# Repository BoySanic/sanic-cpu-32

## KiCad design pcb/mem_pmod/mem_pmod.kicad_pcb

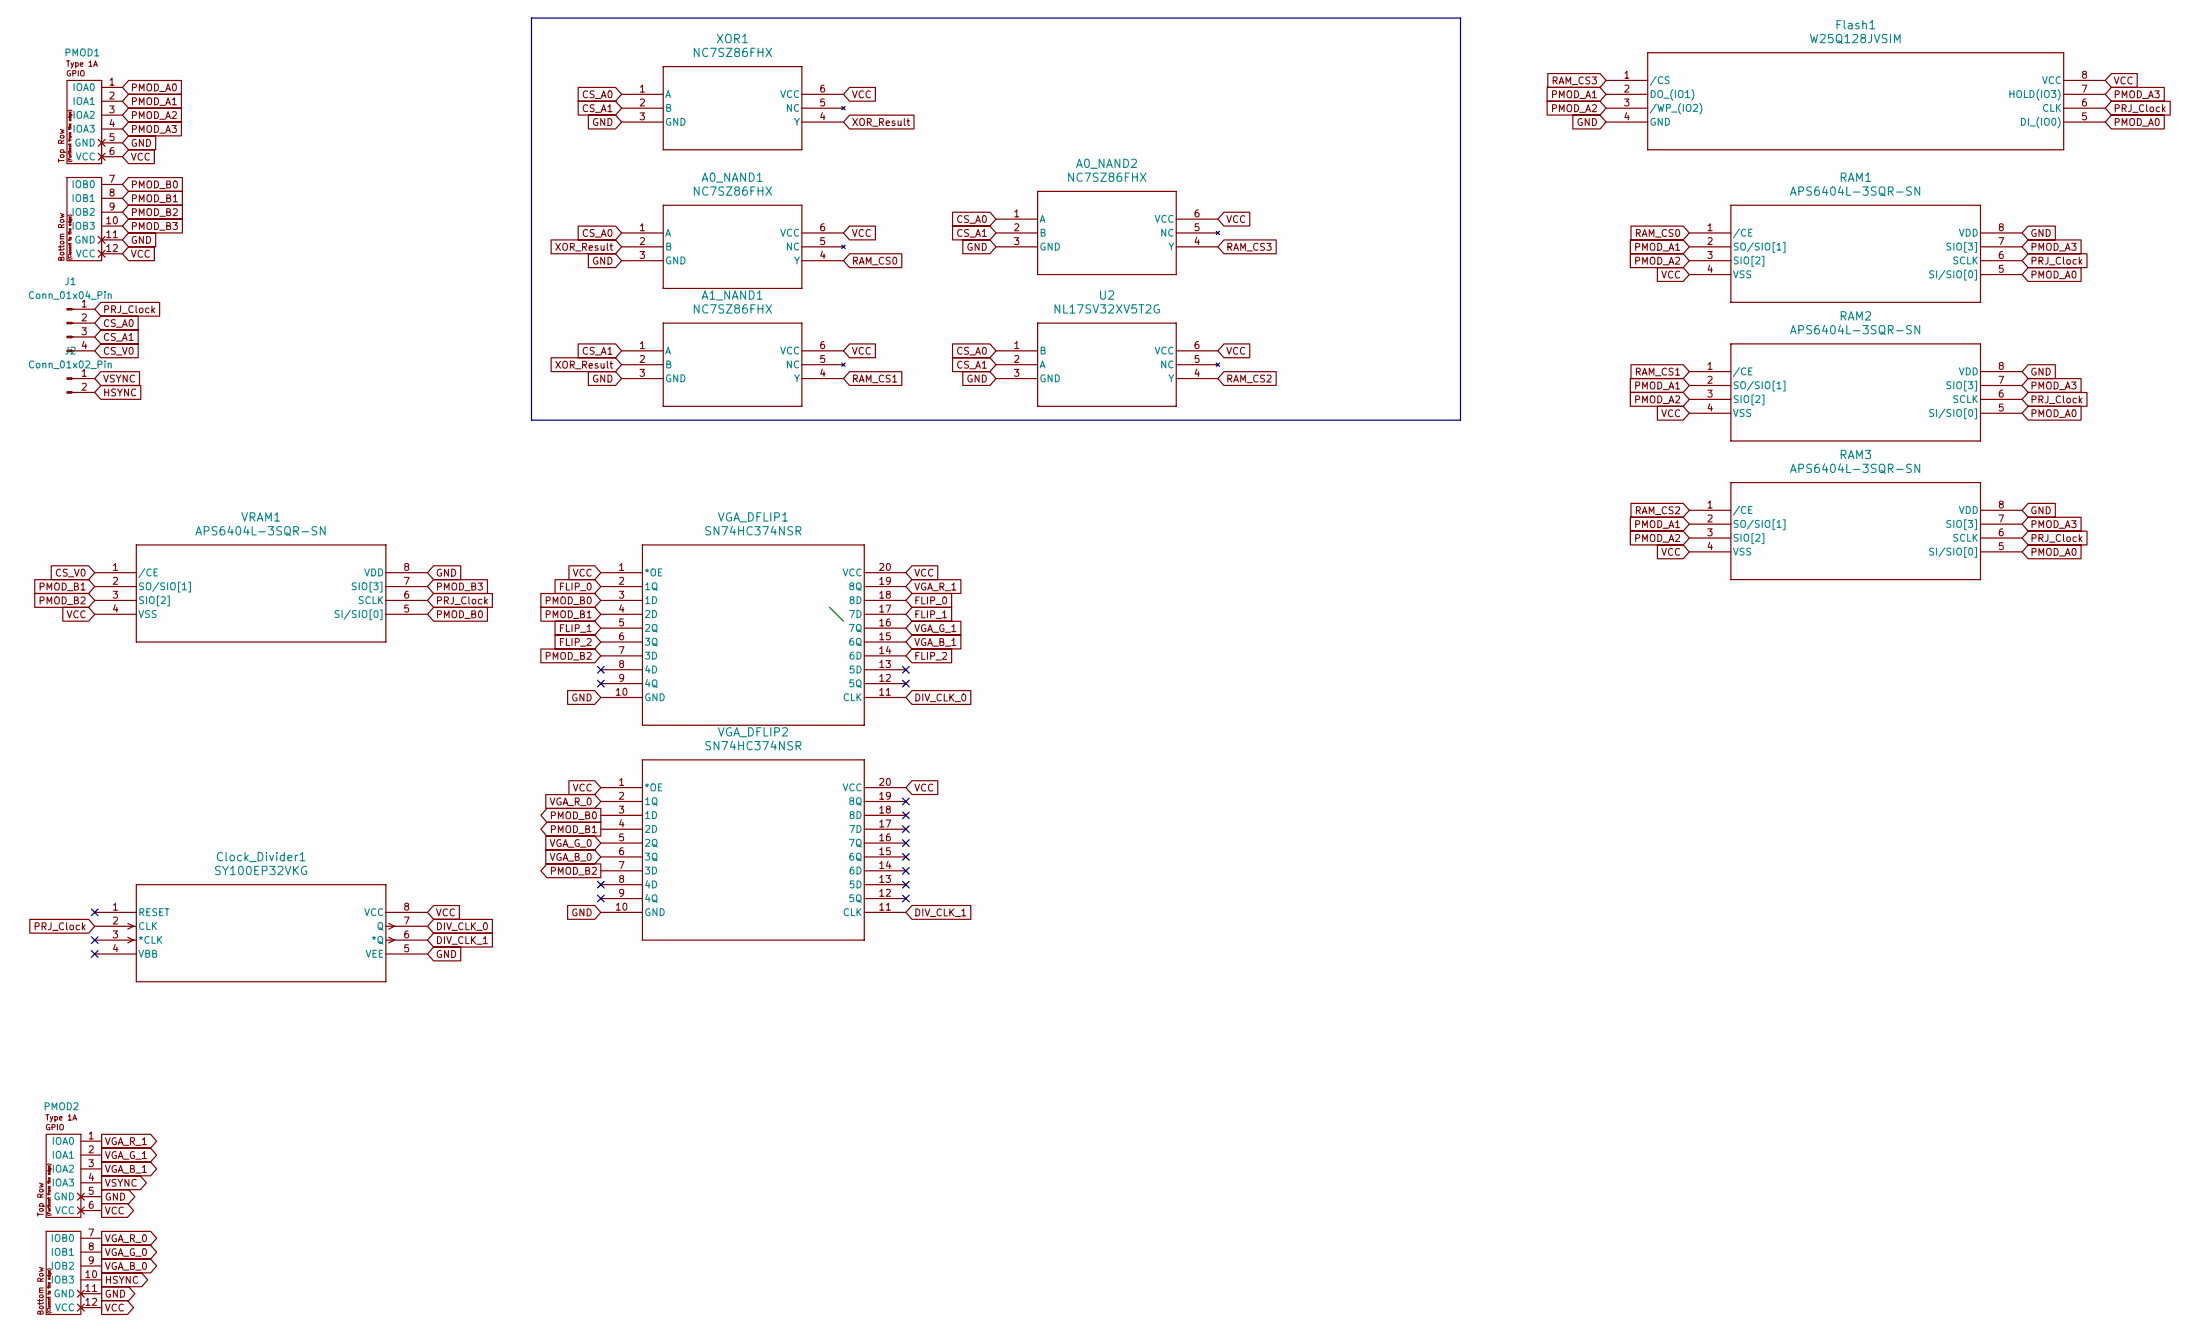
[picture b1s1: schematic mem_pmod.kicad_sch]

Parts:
A0_NAND1, A0_NAND2, A1_NAND1: NC7SZ86FHX; MICROPAK2-6_1X1_ONS
Clock_Divider1: SY100EP32VKG; MSOP-8_K8-1_MCL
Flash1: W25Q128JVSIM; SOIC_128JVSIM_WIN
J1: Conn_01x04_Pin; PinHeader_1x04_P2.54mm_Horizontal
J2: Conn_01x02_Pin; PinHeader_1x02_P2.54mm_Horizontal
PMOD1, PMOD2: PMOD-Device-x2-Type-1A-GPIO; pmod_pin_array_6x2
RAM1, RAM2, RAM3: APS6404L-3SQR-SN; APS6404L-3SQR-SN_APY
U2: NL17SV32XV5T2G; SOT553-5_ONS
VGA_DFLIP1, VGA_DFLIP2: SN74HC374NSR; NS20
VRAM1: APS6404L-3SQR-SN; APS6404L-3SQR-SN_APY
XOR1: NC7SZ86FHX; MICROPAK2-6_1X1_ONS

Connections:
CS_A0: A0_NAND1.1 (A), A0_NAND2.1 (A), J1.2, U2.1 (B), XOR1.1 (A)
CS_A1: A0_NAND2.2 (B), A1_NAND1.1 (A), J1.3, U2.2 (A), XOR1.2 (B)
CS_V0: J1.4, VRAM1.1 (/CE)
DIV_CLK_0: Clock_Divider1.7 (Q), VGA_DFLIP1.11 (CLK)
DIV_CLK_1: Clock_Divider1.6 (*Q), VGA_DFLIP2.11 (CLK)
FLIP_0: VGA_DFLIP1.2 (1Q), VGA_DFLIP1.18 (8D)
FLIP_1: VGA_DFLIP1.5 (2Q), VGA_DFLIP1.17 (7D)
FLIP_2: VGA_DFLIP1.6 (3Q), VGA_DFLIP1.14 (6D)
GND: A0_NAND1.3 (GND), A0_NAND2.3 (GND), A1_NAND1.3 (GND), Clock_Divider1.5 (VEE), Flash1.4 (GND), PMOD1.5 (GND), PMOD1.11 (GND), PMOD2.5 (GND), PMOD2.11 (GND), RAM1.8 (VDD), RAM2.8 (VDD), RAM3.8 (VDD), U2.3 (GND), VGA_DFLIP1.10 (GND), VGA_DFLIP2.10 (GND), VRAM1.8 (VDD), XOR1.3 (GND)
HSYNC: J2.2, PMOD2.10 (IOB3)
PMOD_A0: Flash1.5 (DI_(IO0)), PMOD1.1 (IOA0), RAM1.5 (SI/SIO[0]), RAM2.5 (SI/SIO[0]), RAM3.5 (SI/SIO[0])
PMOD_A1: Flash1.2 (DO_(IO1)), PMOD1.2 (IOA1), RAM1.2 (SO/SIO[1]), RAM2.2 (SO/SIO[1]), RAM3.2 (SO/SIO[1])
PMOD_A2: Flash1.3 (/WP_(IO2)), PMOD1.3 (IOA2), RAM1.3 (SIO[2]), RAM2.3 (SIO[2]), RAM3.3 (SIO[2])
PMOD_A3: Flash1.7 (HOLD(IO3)), PMOD1.4 (IOA3), RAM1.7 (SIO[3]), RAM2.7 (SIO[3]), RAM3.7 (SIO[3])
PMOD_B0: PMOD1.7 (IOB0), VGA_DFLIP1.3 (1D), VGA_DFLIP2.3 (1D), VRAM1.5 (SI/SIO[0])
PMOD_B1: PMOD1.8 (IOB1), VGA_DFLIP1.4 (2D), VGA_DFLIP2.4 (2D), VRAM1.2 (SO/SIO[1])
PMOD_B2: PMOD1.9 (IOB2), VGA_DFLIP1.7 (3D), VGA_DFLIP2.7 (3D), VRAM1.3 (SIO[2])
PMOD_B3: PMOD1.10 (IOB3), VRAM1.7 (SIO[3])
PRJ_Clock: Clock_Divider1.2 (CLK), Flash1.6 (CLK), J1.1, RAM1.6 (SCLK), RAM2.6 (SCLK), RAM3.6 (SCLK), VRAM1.6 (SCLK)
RAM_CS0: A0_NAND1.4 (Y), RAM1.1 (/CE)
RAM_CS1: A1_NAND1.4 (Y), RAM2.1 (/CE)
RAM_CS2: RAM3.1 (/CE), U2.4 (Y)
RAM_CS3: A0_NAND2.4 (Y), Flash1.1 (/CS)
VCC: A0_NAND1.6 (VCC), A0_NAND2.6 (VCC), A1_NAND1.6 (VCC), Clock_Divider1.8 (VCC), Flash1.8 (VCC), PMOD1.6 (VCC), PMOD1.12 (VCC), PMOD2.6 (VCC), PMOD2.12 (VCC), RAM1.4 (VSS), RAM2.4 (VSS), RAM3.4 (VSS), U2.6 (VCC), VGA_DFLIP1.1 (*OE), VGA_DFLIP1.20 (VCC), VGA_DFLIP2.1 (*OE), VGA_DFLIP2.20 (VCC), VRAM1.4 (VSS), XOR1.6 (VCC)
VGA_B_0: PMOD2.9 (IOB2), VGA_DFLIP2.6 (3Q)
VGA_B_1: PMOD2.3 (IOA2), VGA_DFLIP1.15 (6Q)
VGA_G_0: PMOD2.8 (IOB1), VGA_DFLIP2.5 (2Q)
VGA_G_1: PMOD2.2 (IOA1), VGA_DFLIP1.16 (7Q)
VGA_R_0: PMOD2.7 (IOB0), VGA_DFLIP2.2 (1Q)
VGA_R_1: PMOD2.1 (IOA0), VGA_DFLIP1.19 (8Q)
VSYNC: J2.1, PMOD2.4 (IOA3)
XOR_Result: A0_NAND1.2 (B), A1_NAND1.2 (B), XOR1.4 (Y)

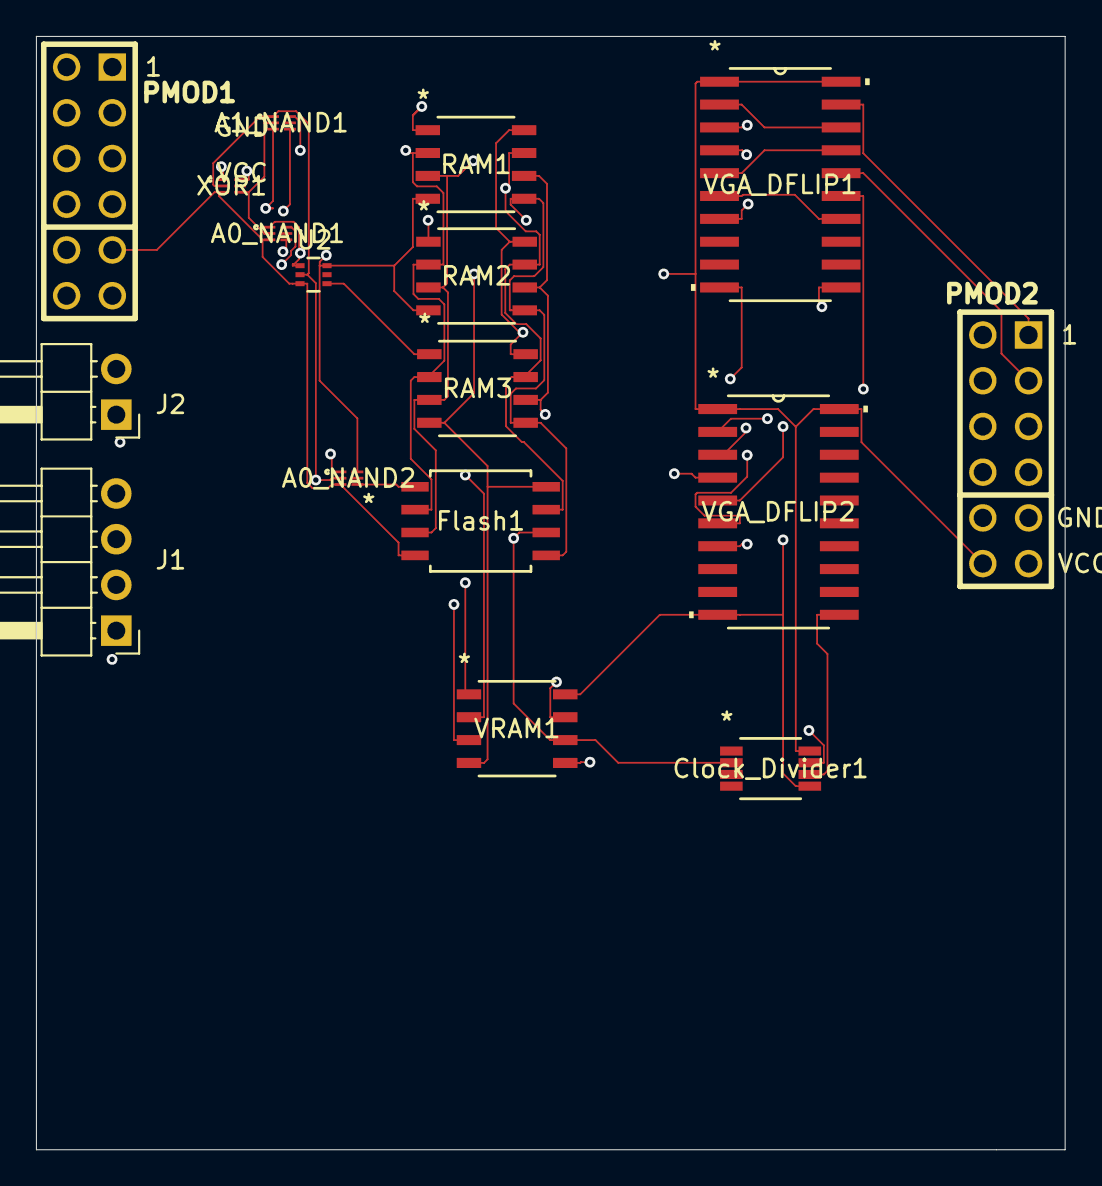
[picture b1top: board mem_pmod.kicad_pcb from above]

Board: 4 copper layers, 57.1 x 61.8 mm, 17 parts (0 on the bottom side), 32 nets.

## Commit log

2025-10-06 Committing before I replace opcode logic with a demux
2025-10-09 we have cognitiongit status!
2025-11-19 Grabbed files
2025-11-22 Store works! As does LIU. IR can receive instructions from arbitrary places in memory too.
2025-11-22 Move ISA.md to readme
2025-12-14 Latest changes
2025-12-14 Fixed memory access somewhat
2025-12-14 Fixed memory access (pla and asm)
2025-12-24 Tested register file, fixed ALU, tested control unit somewhat
2025-12-26 Add kicad pcb stuff and some modifications to logisim apparently
2025-12-26 continue working on schematic
2025-12-28 more or less completed schematic. Still needs caps/resistors or whatever
2025-12-28 Add tinyvga and remove autosaves
2025-12-28 Abstracted CS stuff away into another sheet
2025-12-29 change vram wiring
2026-02-10 Add comment support
    Updated hello_world.asm and prompt.asm to have comments
    Fixes #8
2026-02-10 Mark unused Uops
2026-02-11 Only emit memory address when MEM_ADDR_EMIT is high. Prevents issues with peripherals, mostly.
2026-02-11 Optimized load instruction that was needlessly 1 cycle too long
2026-02-11 Re-added reg clear signal since it is used but was just never implemented. implemented it as well.
2026-02-11 Started work on command interpreter, identified needs for assembler
2026-02-11 Added labels Fixes #12
2026-02-11 Added assembler variables Fixes #14
2026-02-12 Add push/pop and call/ret instructions
    push/pop are working and tested, call/ret are not tested
    Fixes #7
2026-02-12 Debugged/tested call/return instructions Adjusted inspector.py to take a parameter for the file, and to print 4 bytes per line instead of all in one line.
    Created call.asm to test the call/return functionality
    Adapted assembler to fix bugs related to call/return and labels in
    general.
    Added/repurposed signals in pla to make this stuff work.
    Fixes #17
    Fixes #16
2026-02-13 Fixed variables and labels a tiny bit more. There's a bug still where if you put a comment on the same line as a label it freaks the hell out. That can use some improvement.
2026-02-13 Add wood command to interpretor
2026-02-17 Fixed some interpreter bugs
2026-02-18 Fixed labels, existing assembly needs updating to not use the : char at the beginning to signify a reference to a label
2026-02-19 Fixed issues microcode: - push/pop were using byte mode, not quad byte mode, so we were only pushing/popping one byte - CALLI didn't have quadbyte set either, so it was pushing a byte instead of the 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
2026-02-20 Started C rewrite of assembler
2026-02-21 Add sc32-as.py
2026-02-21 Make --out required
2026-02-22 Add sc32-as.py (#21)
    * Add sc32-as.py
    * Fix opcodes of OR[I] and AND[I]
    * Fix typo in AMOV mnemonic
    * Make --out required
    * Fix opcodes of conditional jumps
    * Support section directive
2026-02-22 Various bugfixes in the circuit for byte-addressed instructions Fixed microcode bugs Added labels flag
2026-02-22 Memory is byte-addressed. Add CALL instruction to pla-gen.py MEM_QUADBYTE signal tells the memory to output 4 bytes on its quad output, so it functions like it used to. Side effect is we get 1/4th of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
2026-02-23 Assembler cleanup and change print symbol formatting
2026-06-12 Support ALIGN and DD
2026-06-17 Add clock counter device to peripheral bus, use a mux instead of the raw pins to address devices, more c and assembly code
2026-06-17 Make changes to assembler to allow duplicate labels for each file (which aren't external dependencies)
